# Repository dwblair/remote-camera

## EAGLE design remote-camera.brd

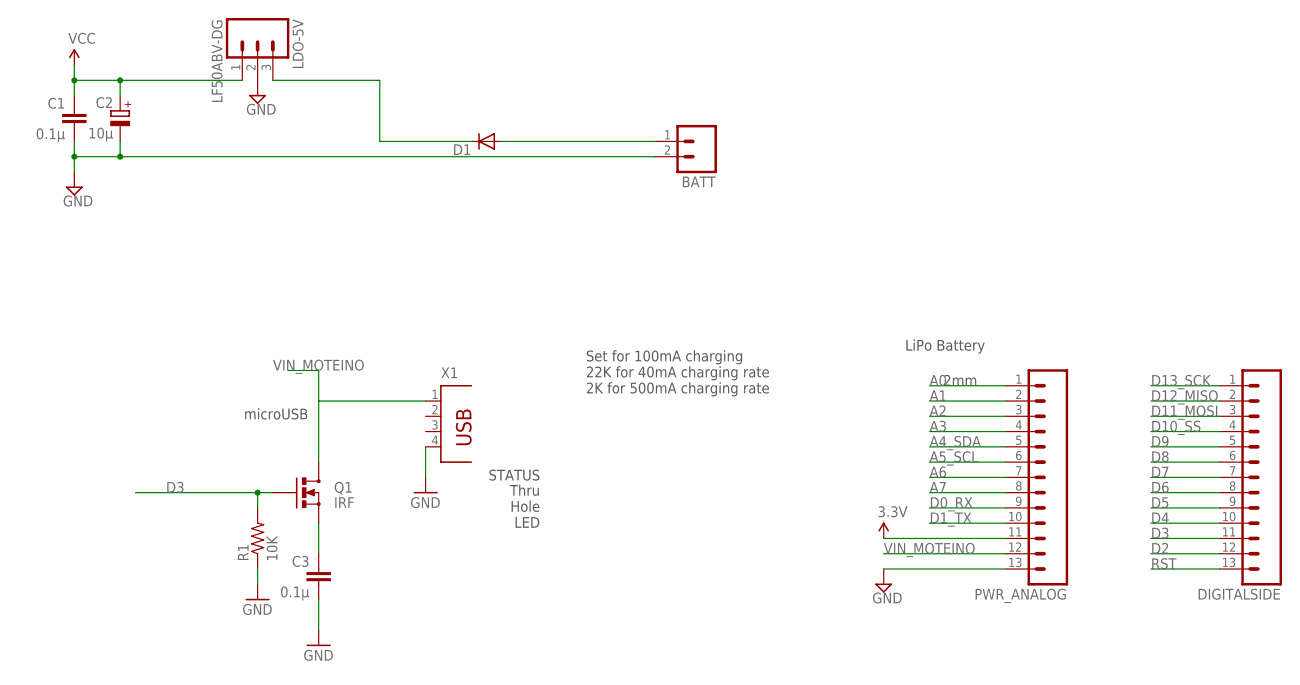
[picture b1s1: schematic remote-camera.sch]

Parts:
BATT: M02PTH; 1X02
C1, C3: 0.1µ; C025-024X044
C2: 10µ; E1,8-4
D1: DIODE-D-5; D-5
DIGITALSIDE: HDR_13PINREGULAR; 1X13
LDO-5V: LF50ABV-DG; 1X03
PWR_ANALOG: HDR_13PINREGULAR; 1X13
Q1: IRF; TO220V
R1: 10K; AXIAL-0.3
X1: PN87520

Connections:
A0: PWR_ANALOG.1
A1: PWR_ANALOG.2
A2: PWR_ANALOG.3
A3: PWR_ANALOG.4
A4_SDA: PWR_ANALOG.5
A5_SCL: PWR_ANALOG.6
A6: PWR_ANALOG.7
A7: PWR_ANALOG.8
D0_RX: PWR_ANALOG.9
D1_TX: PWR_ANALOG.10
D2: DIGITALSIDE.12
D3: DIGITALSIDE.11, Q1.1 (G), R1.P$2 (2)
D4: DIGITALSIDE.10
D5: DIGITALSIDE.9
D6: DIGITALSIDE.8
D7: DIGITALSIDE.7
D8: DIGITALSIDE.6
D9: DIGITALSIDE.5
D10_SS: DIGITALSIDE.4
D11_MOSI: DIGITALSIDE.3
D12_MISO: DIGITALSIDE.2
D13_SCK: DIGITALSIDE.1
GND: BATT.2, C1.2, C2.-, C3.2, LDO-5V.2, PWR_ANALOG.13, R1.P$1 (1), X1.4
unnamed: BATT.1, D1.A
unnamed: C3.1, Q1.3 (S)
unnamed: D1.C, LDO-5V.3
RST: DIGITALSIDE.13
VCC: C1.1, C2.+, LDO-5V.1, PWR_ANALOG.11
VIN_MOTEINO: PWR_ANALOG.12, Q1.2 (D), X1.1

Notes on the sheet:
Set for 100mA charging 22K for 40mA charging rate 2K for 500mA charging rate
LiPo Battery
2mm
microUSB
Thru Hole LED
STATUS

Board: 2 copper layers, 11 parts (0 on the bottom side), 7 nets, no tracks yet.

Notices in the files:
parts and their libraries:
SparkFun-Connectors: Licensing: Creative Commons ShareAlike 4.0 International - https://creativecommons.org/licenses/by-sa/4.0
